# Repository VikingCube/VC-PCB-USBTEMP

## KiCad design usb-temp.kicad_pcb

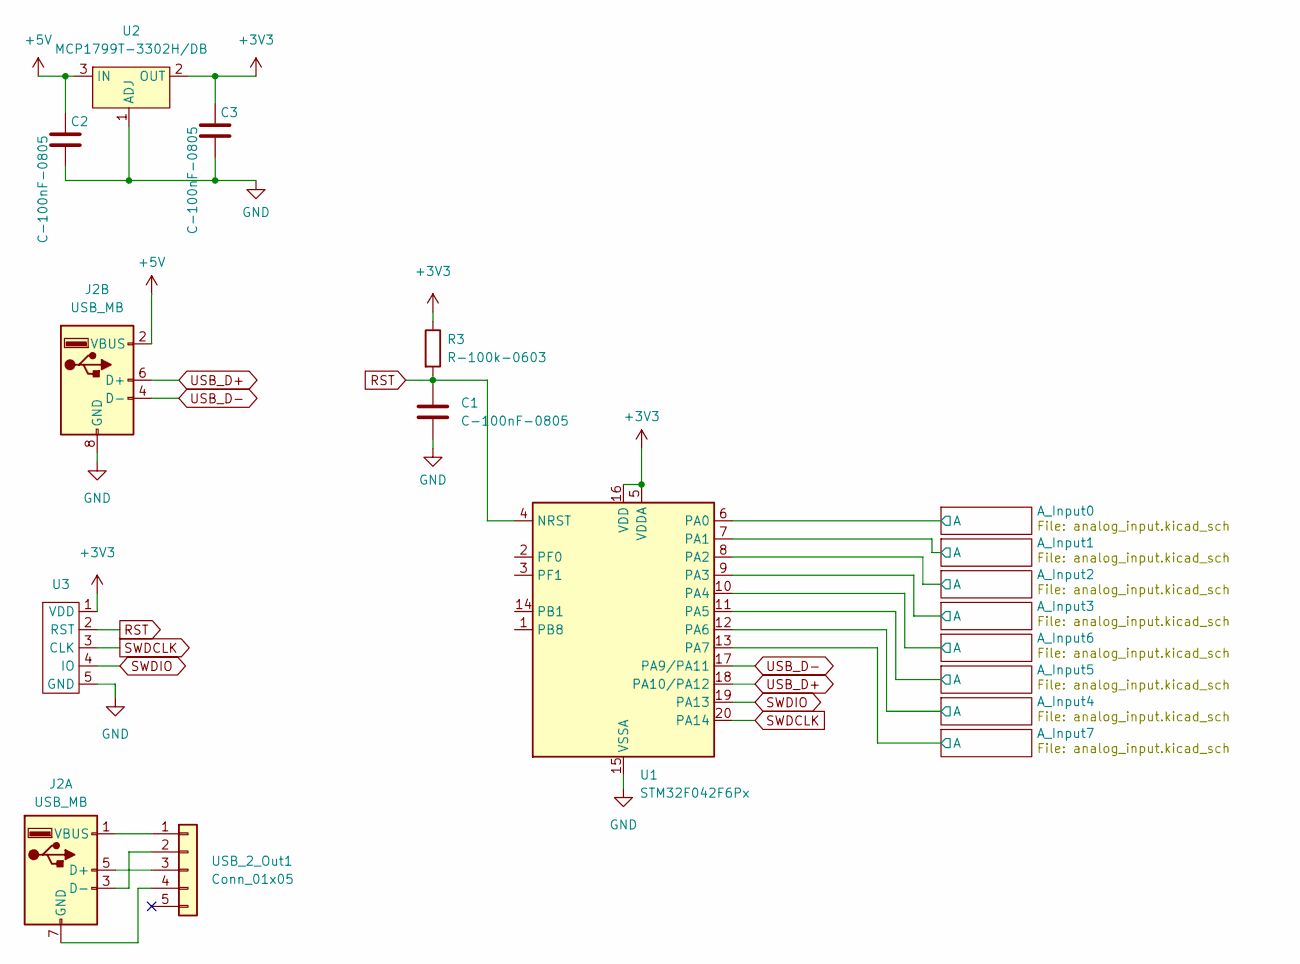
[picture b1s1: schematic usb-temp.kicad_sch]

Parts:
C1, C2, C3: C-100nF-0805; C_0805_2012Metric_Pad1.18x1.45mm_HandSolder
J2: USB_MB; MB_USB
R3: R-100k-0603; R_0603_1608Metric
U1: STM32F042F6Px; TSSOP-20_4.4x6.5mm_P0.65mm
U2: MCP1799T-3302H/DB; SOT-223
U3: 1.27 SWD Programmer
USB_2_Out1: Conn_01x05; PinHeader_1x05_P2.54mm_Vertical

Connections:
+3V3: C3.1, R3.1, U1.5 (VDDA), U1.16 (VDD), U2.2 (OUT), U2.4 (OUT), U3.1 (VDD); also elsewhere on the board
+5V: C2.1, J2.2 (VBUS), U2.3 (IN)
/A_Input0/A: U1.6 (PA0); also elsewhere on the board
/A_Input2/A: U1.8 (PA2); also elsewhere on the board
/A_Input3/A: U1.9 (PA3); also elsewhere on the board
/A_Input4/A: U1.12 (PA6); also elsewhere on the board
/A_Input5/A: U1.11 (PA5); also elsewhere on the board
/A_Input6/A: U1.10 (PA4); also elsewhere on the board
/A_Input7/A: U1.13 (PA7); also elsewhere on the board
GND: C1.2, C2.2, C3.2, J2.8 (GND), U1.15 (VSSA), U2.1 (ADJ), U3.5 (GND); also elsewhere on the board
unnamed: J2.5 (D+), USB_2_Out1.3
unnamed: J2.3 (D-), USB_2_Out1.2
unnamed: J2.7 (GND), USB_2_Out1.4
unnamed: J2.1 (VBUS), USB_2_Out1.1
SWDCLK: U1.20 (PA14), U3.3 (CLK)
SWDIO: U1.19 (PA13), U3.4 (IO)
USB_D+: J2.6 (D+), U1.18 (PA10/PA12)
USB_D-: J2.4 (D-), U1.17 (PA9/PA11)

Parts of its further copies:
R2: R-100k-0603; R_0603_1608Metric

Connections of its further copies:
+3V3: R2.1; also elsewhere on the board

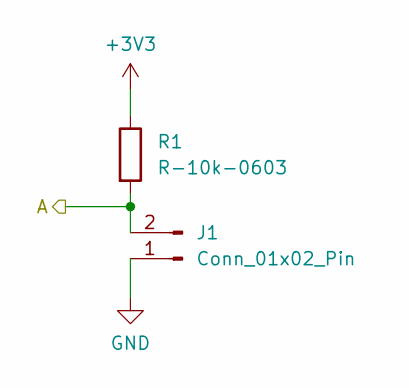
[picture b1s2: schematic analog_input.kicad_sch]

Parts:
J1: Conn_01x02_Pin; PinHeader_1x02_P2.54mm_Vertical
R1: R-10k-0603; R_0603_1608Metric_Pad0.98x0.95mm_HandSolder

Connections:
+3V3: R1.1; also elsewhere on the board
/A_Input0/A: J1.2, R1.2; also elsewhere on the board
GND: J1.1; also elsewhere on the board

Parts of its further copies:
J4, J5, J6, J7, J8, J9, J10: Conn_01x02_Pin; PinHeader_1x02_P2.54mm_Vertical
R4, R5, R6, R7, R8, R9: R-10k-0603; R_0603_1608Metric_Pad0.98x0.95mm_HandSolder

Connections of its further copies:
+3V3: R4.1, R5.1, R6.1, R7.1, R8.1, R9.1; also elsewhere on the board
/A_Input2/A: J5.2, R4.2; also elsewhere on the board
/A_Input3/A: J6.2, R5.2; also elsewhere on the board
/A_Input4/A: J9.2, R8.2; also elsewhere on the board
/A_Input5/A: J8.2, R7.2; also elsewhere on the board
/A_Input6/A: J7.2, R6.2; also elsewhere on the board
/A_Input7/A: J10.2, R9.2; also elsewhere on the board
GND: J4.1, J5.1, J6.1, J7.1, J8.1, J9.1, J10.1; also elsewhere on the board

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
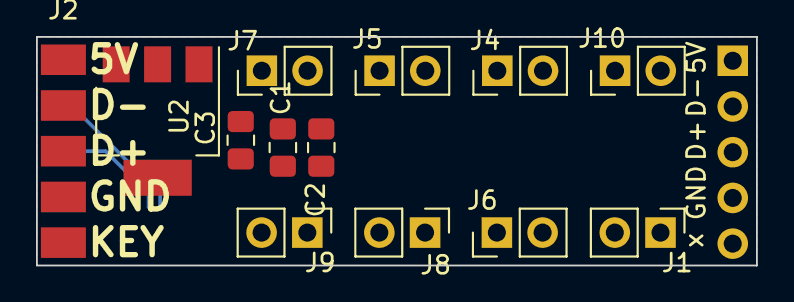
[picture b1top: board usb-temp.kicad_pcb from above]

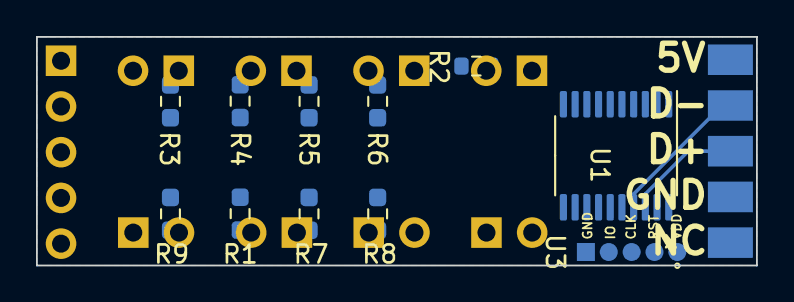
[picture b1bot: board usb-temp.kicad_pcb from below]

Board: 4 copper layers, 40.0 x 12.7 mm, 25 parts (11 on the bottom side), 20 nets.

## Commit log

2023-08-20 first
2023-12-01 First Order
2023-12-01 First order 2nd try
2023-12-02 new stab, as old is deprecated
2023-12-16 no idea
2024-01-18 Switching to new desing, small swd
    working on v2.0
2024-09-05 vip
    vip
